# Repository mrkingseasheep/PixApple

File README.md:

# PixApple

PixApple is designed as a RP2040 breakout board. It features 8 general use GPIOs, 1 SPI interface, 1 I2C interface, 4 ADC channels, 4 PWM channels and a CAN bus.
I designed it because I wanted a board that I could use for general purpose robotics projects. Being from FRC, a CAN bus was a must so I added the CAN bus onto the RP2040 with split terminations.
The Roborio is like 2000CAD so it's so far out of reach its funny. Of course, I don't need the real time OS or the robust nature of the thing, I just want to drive a lil car or something. So I created this!
Building this project really gave me a greater understanding of what went on undernearth the Roborio (I never did open it) and everything actually kinda makes sense now.
I chose the RP2040 because it is cheap, decently powerful for the basic robotics I plan on doing with it and is also what I'm used to.
Additionally, I chose the 0603 SMT format because I wanted to be able to fix any problems I have later on with this board.
This being V1.0, many of the values are not tested and I wanted the ability to fix them if anything happened.
Finally, there are test points scattered around the board for easy debugging.

## What I've gained

Total time spent: 51 hours (I'm still so slow at KiCAD) (the redo didn't help)

This is my first semi-intermediate project and I wanted to learn more about ICs in general. I've incorporated: wide power traces, equal length wires and a ground pour on top and bottom in this project.

## BOM

| Quantity | Value                       | Cost    | URL                                                                                                                                                    |
| -------- | --------------------------- | ------- | ------------------------------------------------------------------------------------------------------------------------------------------------------ |
| 17       | Capacitor 100n              | 0.068   | https://www.aliexpress.com/item/1005002782324319.html                                                                                                  |
| 3        | Capacitor 1u                | 0.012   | https://www.aliexpress.com/item/1005002782324319.html                                                                                                  |
| 2        | Capacitor 10n               | 0.008   | https://www.aliexpress.com/item/1005002782324319.html                                                                                                  |
| 2        | Capacitor 10u               | 0.008   | https://www.aliexpress.com/item/1005002782324319.html                                                                                                  |
| 1        | Capacitor 4.7n              | 0.004   | https://www.aliexpress.com/item/1005002782324319.html                                                                                                  |
| 2        | TVS Diode RCLAMP0502BA      | 2.50    | https://www.digikey.ca/en/products/detail/semtech-corporation/RCLAMP0502BATCT/2603604?s=N4IgTCBcDaICoDUDKACAIgSwPYBMCmKASgMIAyAggLIAKADAKy1gBC5IAugL5A |
| 1        | SMF5V0A                     | 0.25    | https://www.digikey.ca/en/products/detail/vishay-general-semiconductor-diodes-division/SMF5V0A-E3-08/1680585                                           |
| 1        | 1N4148W                     | 0.014   | https://www.aliexpress.com/item/4000685043735.html                                                                                                     |
| 3        | LED                         | 0.0525  | https://www.aliexpress.com/item/1005006211269173.html                                                                                                  |
| 1        | USB_C_Receptacle_USB2.0_16P | 0.1875  | https://www.aliexpress.com/item/1005008515699009.html                                                                                                  |
| 22       | 2.54mm Pins Male            | 0.20295 | https://www.aliexpress.com/item/4001198421663.html                                                                                                     |
| 2        | Resistor 27R                | 0.01    | https://www.aliexpress.com/item/1005007902452631.html                                                                                                  |
| 3        | Resistor 1K                 | 0.015   | https://www.aliexpress.com/item/1005007902452631.html                                                                                                  |
| 5        | Resistor DNF                | 0.025   | https://www.aliexpress.com/item/1005007902452631.html                                                                                                  |
| 2        | Resistor 60R                | 0.01    | https://www.aliexpress.com/item/1005007902452631.html                                                                                                  |
| 5        | Resistor 10K                | 0.025   | https://www.aliexpress.com/item/1005007902452631.html                                                                                                  |
| 3        | Resistor 220R               | 0.015   | https://www.aliexpress.com/item/1005007902452631.html                                                                                                  |
| 2        | Resistor 5.1K               | 0.01    | https://www.aliexpress.com/item/1005007902452631.html                                                                                                  |
| 1        | RP2040                      | 1.29    | https://www.canakit.com/raspberry-pi-rp2040.html?cid=cad&src=raspberrypi                                                                               |
| 1        | W25Q128JVS                  |         | JLCPCB Assembly                                                                                                                                        |
| 1        | NCP1117-3.3_SOT223          |         | JLCPCB Assembly                                                                                                                                        |
| 1        | MCP2515-xSO                 |         | JLCPCB Assembly                                                                                                                                        |
| 1        | TCAN337G                    |         | JLCPCB Assembly                                                                                                                                        |
| 1        | ASE-12MHz                   | 1.56    | https://www.mouser.ca/ProductDetail/ABRACON/ASE-12.000MHZ-ET?qs=uDmhV2jwPRcj2BLg3gv24Q%3D%3D                                                           |
| 1        | ASE-16MHz                   | 1.53    | https://www.mouser.ca/ProductDetail/ABRACON/ASE-16.000MHZ-LC-T?qs=gt1LBUVyoHnfDWzQTg2whA%3D%3D                                                         |
| 1        | PCB                         | 75      | JLCPCB Assembly                                                                                                                                        |
| 2        | Heat set insert             | 0.10    | https://www.aliexpress.com/item/1005007653131713.html                                                                                                  |
| 2        | M2                          | 0.08    | https://www.aliexpress.com/item/32810872544.html                                                                                                       |
| 1        | Case                        | 5       | Printing Legion                                                                                                                                        |

Total: 80 CAD

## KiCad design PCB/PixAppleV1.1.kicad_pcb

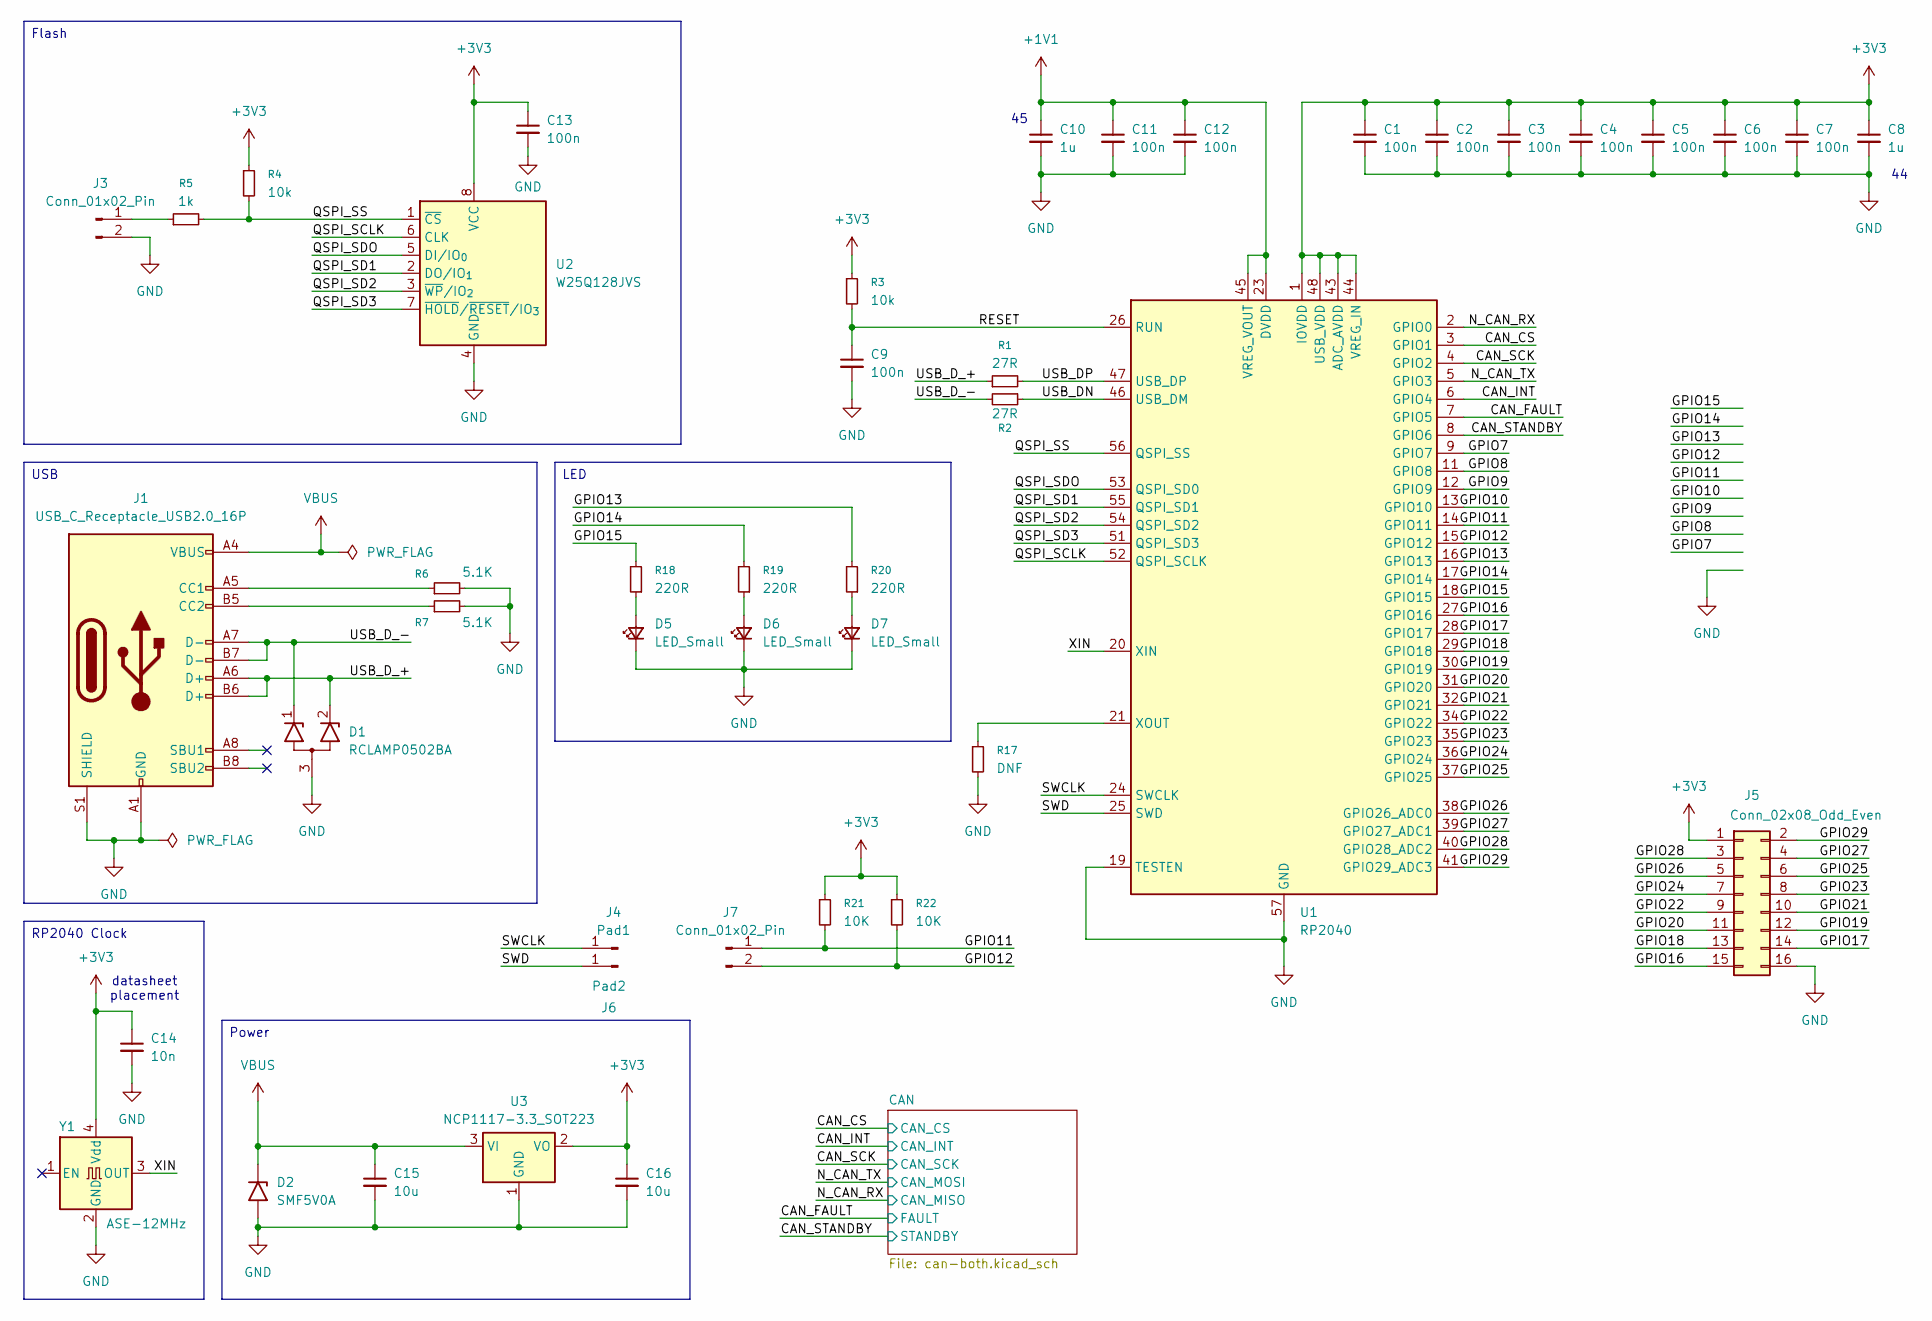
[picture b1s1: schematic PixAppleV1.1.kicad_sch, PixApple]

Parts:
C1, C2, C3, C4, C5, C6, C7, C9, C11, C12, C13: 100n; C_0603_1608Metric_Pad1.08x0.95mm_HandSolder
C8, C10: 1u; C_0603_1608Metric_Pad1.08x0.95mm_HandSolder
C14: 10n; C_0603_1608Metric_Pad1.08x0.95mm_HandSolder
C15, C16: 10u; C_0603_1608Metric_Pad1.08x0.95mm_HandSolder
D1: RCLAMP0502BA; SOT-416
D2: SMF5V0A; D_SMF
D5, D6, D7: LED_Small; LED_0603_1608Metric_Pad1.05x0.95mm_HandSolder
J1: USB_C_Receptacle_USB2.0_16P; USB_C_Receptacle_GCT_USB4105-xx-A_16P_TopMnt_Horizontal
J3, J7: Conn_01x02_Pin; PinHeader_1x02_P2.54mm_Vertical
J4: Pad1; TestPoint_Pad_1.0x1.0mm
J5: Conn_02x08_Odd_Even; PinHeader_2x08_P2.54mm_Vertical
J6: Pad2; TestPoint_Pad_1.0x1.0mm
R1, R2: 27R; R_0603_1608Metric_Pad0.98x0.95mm_HandSolder
R3, R4: 10k; R_0603_1608Metric_Pad0.98x0.95mm_HandSolder
R5: 1k; R_0603_1608Metric_Pad0.98x0.95mm_HandSolder
R6, R7: 5.1K; R_0603_1608Metric_Pad0.98x0.95mm_HandSolder
R17: DNF; R_0603_1608Metric_Pad0.98x0.95mm_HandSolder
R18, R19, R20: 220R; R_0603_1608Metric_Pad0.98x0.95mm_HandSolder
R21, R22: 10K; R_0603_1608Metric_Pad0.98x0.95mm_HandSolder
U1: RP2040; QFN-56-1EP_7x7mm_P0.4mm_EP3.2x3.2mm
U2: W25Q128JVS; SOIC-8_5.3x5.3mm_P1.27mm
U3: NCP1117-3.3_SOT223; SOT-223-3_TabPin2
Y1: ASE-12MHz; Oscillator_SMD_Abracon_ASE-4Pin_3.2x2.5mm

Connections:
+1V1: C10.1, C11.1, C12.1, U1.23 (DVDD), U1.45 (VREG_VOUT), U1.50 (DVDD)
+3V3: C1.1, C2.1, C3.1, C4.1, C5.1, C6.1, C7.1, C8.1, C13.1, C14.1, C16.1, J5.1, R3.1, R4.1, R21.1, R22.1, U1.1 (IOVDD), U1.10 (IOVDD), U1.22 (IOVDD), U1.33 (IOVDD), U1.42 (IOVDD), U1.43 (ADC_AVDD), U1.44 (VREG_IN), U1.48 (USB_VDD), U1.49 (IOVDD), U2.8 (VCC), U3.2 (VO), Y1.4 (Vdd); also elsewhere on the board
/CAN_CS: U1.3 (GPIO1); also elsewhere on the board
/CAN_FAULT: U1.7 (GPIO5); also elsewhere on the board
/CAN_INT: U1.6 (GPIO4); also elsewhere on the board
/CAN_SCK: U1.4 (GPIO2); also elsewhere on the board
/CAN_STANDBY: U1.8 (GPIO6); also elsewhere on the board
/GPIO7: U1.9 (GPIO7); also elsewhere on the board
/GPIO8: U1.11 (GPIO8)
/GPIO9: U1.12 (GPIO9); also elsewhere on the board
/GPIO10: U1.13 (GPIO10); also elsewhere on the board
/GPIO11: J7.1, R21.2, U1.14 (GPIO11)
/GPIO12: J7.2, R22.2, U1.15 (GPIO12)
/GPIO13: R20.2, U1.16 (GPIO13)
/GPIO14: R19.2, U1.17 (GPIO14)
/GPIO15: R18.2, U1.18 (GPIO15)
/GPIO16: J5.15, U1.27 (GPIO16)
/GPIO17: J5.14, U1.28 (GPIO17)
/GPIO18: J5.13, U1.29 (GPIO18)
/GPIO19: J5.12, U1.30 (GPIO19)
/GPIO20: J5.11, U1.31 (GPIO20)
/GPIO21: J5.10, U1.32 (GPIO21)
/GPIO22: J5.9, U1.34 (GPIO22)
/GPIO23: J5.8, U1.35 (GPIO23)
/GPIO24: J5.7, U1.36 (GPIO24)
/GPIO25: J5.6, U1.37 (GPIO25)
/GPIO26: J5.5, U1.38 (GPIO26_ADC0)
/GPIO27: J5.4, U1.39 (GPIO27_ADC1)
/GPIO28: J5.3, U1.40 (GPIO28_ADC2)
/GPIO29: J5.2, U1.41 (GPIO29_ADC3)
/N_CAN_RX: U1.2 (GPIO0); also elsewhere on the board
/N_CAN_TX: U1.5 (GPIO3); also elsewhere on the board
/QSPI_SCLK: U1.52 (QSPI_SCLK), U2.6 (CLK)
/QSPI_SD1: U1.55 (QSPI_SD1), U2.2 (DO/IO_{1})
/QSPI_SD2: U1.54 (QSPI_SD2), U2.3 (~WP/IO_{2})
/QSPI_SD3: U1.51 (QSPI_SD3), U2.7 (~HOLD/~RESET/IO_{3})
/QSPI_SDO: U1.53 (QSPI_SD0), U2.5 (DI/IO_{0})
/QSPI_SS: R4.2, R5.2, U1.56 (QSPI_SS), U2.1 (~CS)
/RESET: C9.1, R3.2, U1.26 (RUN)
/SWCLK: J4.1, U1.24 (SWCLK); also elsewhere on the board
/SWD: J6.1, U1.25 (SWD); also elsewhere on the board
/USB_DN: R2.1, U1.46 (USB_DM)
/USB_DP: R1.2, U1.47 (USB_DP)
/USB_D_+: D1.2 (K2), J1.A6 (D+), J1.B6 (D+), R1.1; also elsewhere on the board
/USB_D_-: D1.1 (K1), J1.A7 (D-), J1.B7 (D-), R2.2; also elsewhere on the board
/XIN: U1.20 (XIN), Y1.3 (OUT)
GND: C1.2, C2.2, C3.2, C4.2, C5.2, C6.2, C7.2, C8.2, C9.2, C10.2, C11.2, C12.2, C13.2, C14.2, C15.2, C16.2, D1.3 (A), D2.2 (A2), D5.1 (K), D6.1 (K), D7.1 (K), J1.A1 (GND), J1.A12 (GND), J1.B1 (GND), J1.B12 (GND), J1.S1 (SHIELD), J3.2, J5.16, R6.2, R7.2, R17.2, U1.19 (TESTEN), U1.57 (GND), U2.4 (GND), U3.1 (GND), Y1.2 (GND); also elsewhere on the board
unnamed: D5.2 (A), R18.1
unnamed: D6.2 (A), R19.1
unnamed: D7.2 (A), R20.1
unnamed: J1.A5 (CC1), R6.1
unnamed: J1.B5 (CC2), R7.1
unnamed: J3.1, R5.1
unnamed: R17.1, U1.21 (XOUT)
VBUS: C15.1, D2.1 (A1), J1.A4 (VBUS), J1.A9 (VBUS), J1.B4 (VBUS), J1.B9 (VBUS), U3.3 (VI); also elsewhere on the board

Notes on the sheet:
datasheet placement
RP2040 Clock
Power
LED
USB
Flash

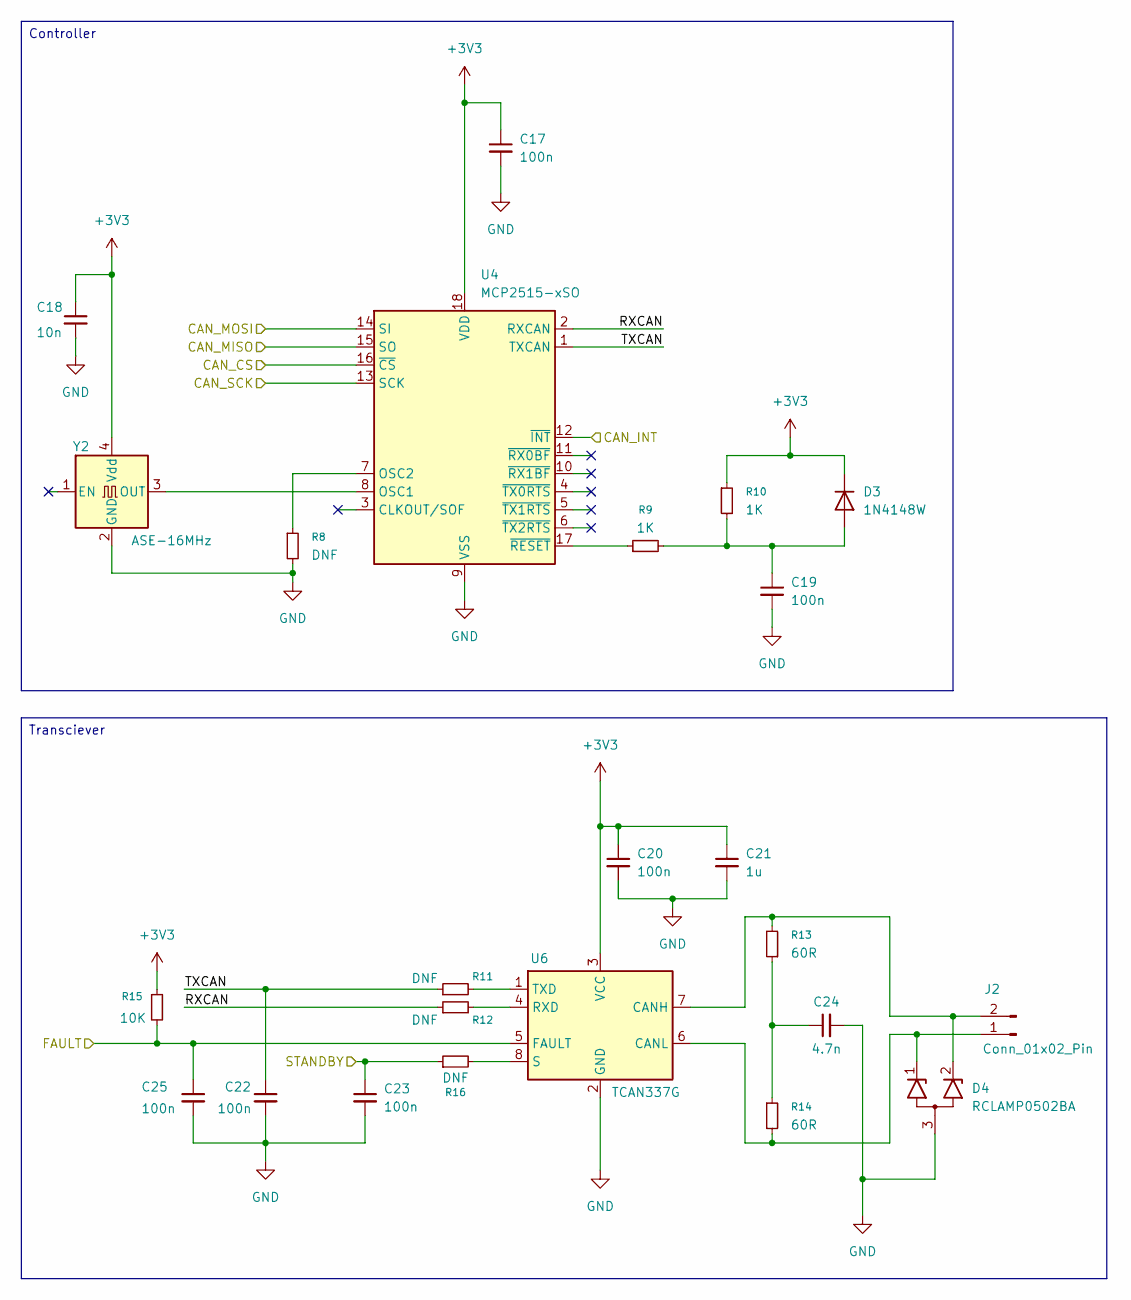
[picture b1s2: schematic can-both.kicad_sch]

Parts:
C17, C19, C20, C22, C23, C25: 100n; C_0603_1608Metric_Pad1.08x0.95mm_HandSolder
C18: 10n; C_0603_1608Metric_Pad1.08x0.95mm_HandSolder
C21: 1u; C_0603_1608Metric_Pad1.08x0.95mm_HandSolder
C24: 4.7n; C_0603_1608Metric_Pad1.08x0.95mm_HandSolder
D3: 1N4148W; D_SOD-123
D4: RCLAMP0502BA; SOT-416
J2: Conn_01x02_Pin; PinHeader_1x02_P2.54mm_Vertical
R8, R11, R12, R16: DNF; R_0603_1608Metric_Pad0.98x0.95mm_HandSolder
R9, R10: 1K; R_0603_1608Metric_Pad0.98x0.95mm_HandSolder
R13, R14: 60R; R_0603_1608Metric_Pad0.98x0.95mm_HandSolder
R15: 10K; R_0603_1608Metric_Pad0.98x0.95mm_HandSolder
U4: MCP2515-xSO; SOIC-18W_7.5x11.6mm_P1.27mm
U6: TCAN337G; SOIC-8_3.9x4.9mm_P1.27mm
Y2: ASE-16MHz; Oscillator_SMD_Abracon_ASE-4Pin_3.2x2.5mm

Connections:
+3V3: C17.1, C18.1, C20.1, C21.1, D3.1 (K), R10.1, R15.1, U4.18 (VDD), U6.3 (VCC), Y2.4 (Vdd); also elsewhere on the board
/CAN/RXCAN: R12.1, U4.2 (RXCAN)
/CAN/TXCAN: C22.1, R11.1, U4.1 (TXCAN)
/CAN_CS: U4.16 (~CS); also elsewhere on the board
/CAN_FAULT: C25.1, R15.2, U6.5 (FAULT); also elsewhere on the board
/CAN_INT: U4.12 (~INT); also elsewhere on the board
/CAN_SCK: U4.13 (SCK); also elsewhere on the board
/CAN_STANDBY: C23.1, R16.1; also elsewhere on the board
/N_CAN_RX: U4.15 (SO); also elsewhere on the board
/N_CAN_TX: U4.14 (SI); also elsewhere on the board
GND: C17.2, C18.2, C19.2, C20.2, C21.2, C22.2, C23.2, C24.2, C25.2, D4.3 (A), R8.2, U4.9 (VSS), U6.2 (GND), Y2.2 (GND); also elsewhere on the board
unnamed: C24.1, R13.1, R14.1
unnamed: C19.1, D3.2 (A), R9.2, R10.2
unnamed: D4.1 (K1), J2.1, R14.2, U6.6 (CANL)
unnamed: D4.2 (K2), J2.2, R13.2, U6.7 (CANH)
unnamed: U4.8 (OSC1), Y2.3 (OUT)
unnamed: R8.1, U4.7 (OSC2)
unnamed: R9.1, U4.17 (~RESET)
unnamed: R12.2, U6.4 (RXD)
unnamed: R16.2, U6.8 (S)
unnamed: R11.2, U6.1 (TXD)

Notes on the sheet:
Transciever
Controller

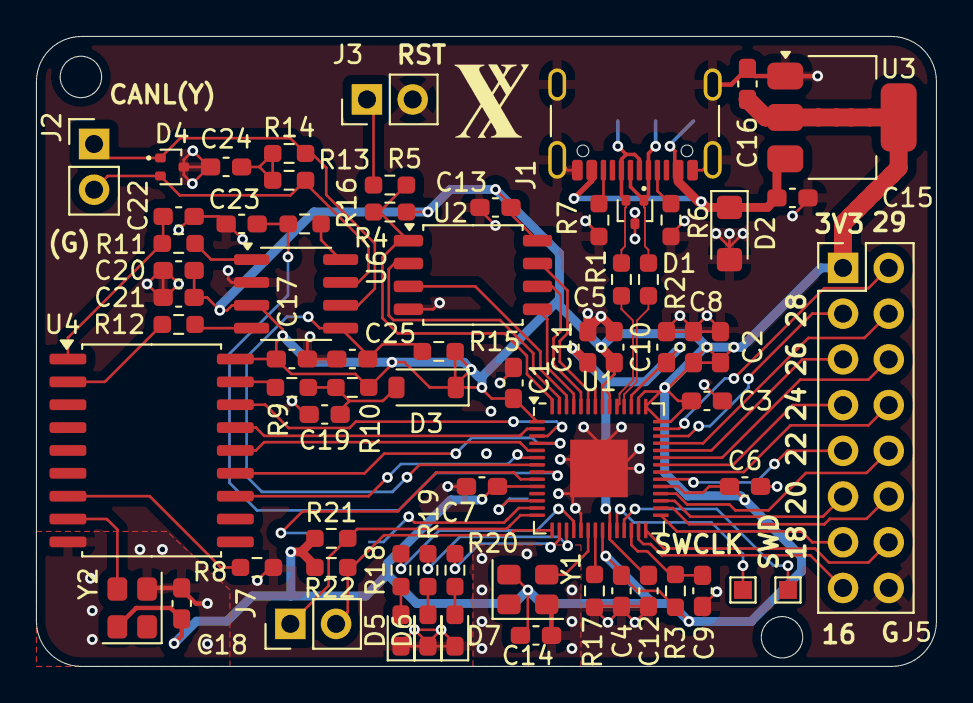
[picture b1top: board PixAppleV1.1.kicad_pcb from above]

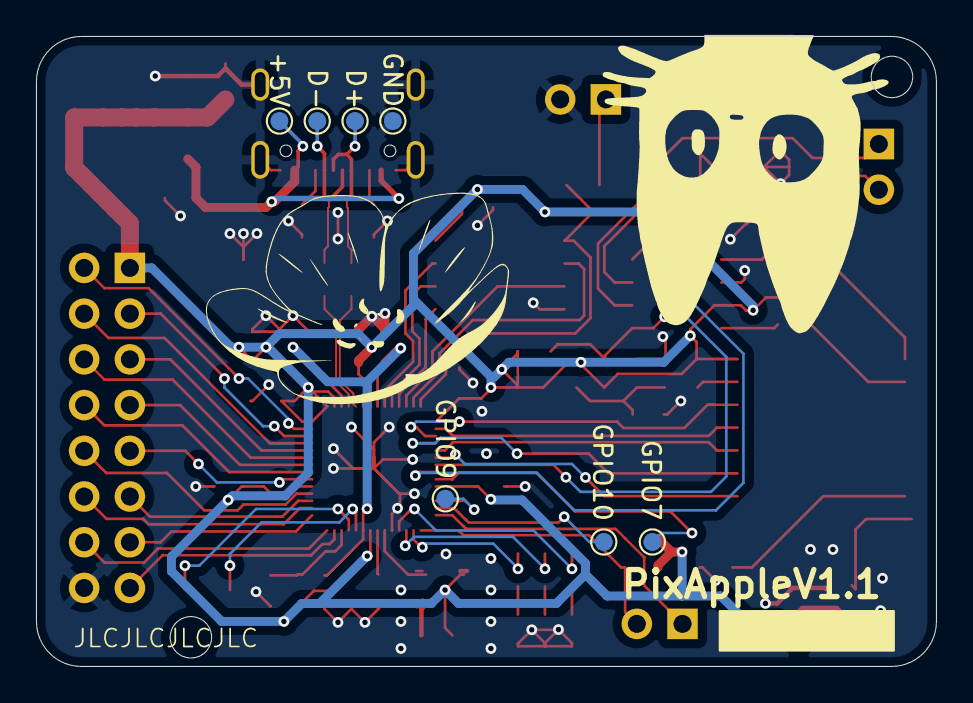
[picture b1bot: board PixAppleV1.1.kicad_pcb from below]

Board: 4 copper layers, 50.0 x 35.0 mm, 75 parts (7 on the bottom side), 66 nets.

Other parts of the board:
+5V: TestPoint_Pad_D1.0mm
D+: TestPoint_Pad_D1.0mm
D-: TestPoint_Pad_D1.0mm
GND: TestPoint_Pad_D1.0mm
GPIO7, GPIO9, GPIO10: TestPoint_Pad_D1.0mm
SWCLK: Pad1; TestPoint_Pad_1.0x1.0mm
SWD: Pad2; TestPoint_Pad_1.0x1.0mm

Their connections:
/GPIO7: GPIO7.1; also elsewhere on the board
/GPIO9: GPIO9.1; also elsewhere on the board
/GPIO10: GPIO10.1; also elsewhere on the board
/SWCLK: SWCLK.1; also elsewhere on the board
/SWD: SWD.1; also elsewhere on the board
/USB_D_+: D+.1; also elsewhere on the board
/USB_D_-: D-.1; also elsewhere on the board
GND: GND.1; also elsewhere on the board
VBUS: +5V.1; also elsewhere on the board

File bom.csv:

"Quantity","Value","Cost","URL"
"17","Capacitor 100n","0.068","https://www.aliexpress.com/item/1005002782324319.html"
"3","Capacitor 1u","0.012","https://www.aliexpress.com/item/1005002782324319.html"
"2","Capacitor 10n","0.008","https://www.aliexpress.com/item/1005002782324319.html"
"2","Capacitor 10u","0.008","https://www.aliexpress.com/item/1005002782324319.html"
"1","Capacitor 4.7n","0.004","https://www.aliexpress.com/item/1005002782324319.html"
"2","TVS Diode RCLAMP0502BA","2.50","https://www.digikey.ca/en/products/detail/semtech-corporatio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"
"1","SMF5V0A","0.25","https://www.digikey.ca/en/products/detail/vishay-general-sem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"
"1","1N4148W","0.014","https://www.aliexpress.com/item/4000685043735.html"
"3","LED","0.0525","https://www.aliexpress.com/item/1005006211269173.html"
"1","USB_C_Receptacle_USB2.0_16P","0.1875","https://www.aliexpress.com/item/1005008515699009.html"
"22","2.54mm Pins Male","0.20295","https://www.aliexpress.com/item/4001198421663.html"
"2","Resistor 27R","0.01","https://www.aliexpress.com/item/1005007902452631.html"
"3","Resistor 1K","0.015","https://www.aliexpress.com/item/1005007902452631.html"
"5","Resistor DNF","0.025","https://www.aliexpress.com/item/1005007902452631.html"
"2","Resistor 60R","0.01","https://www.aliexpress.com/item/1005007902452631.html"
"5","Resistor 10K","0.025","https://www.aliexpress.com/item/1005007902452631.html"
"3","Resistor 220R","0.015","https://www.aliexpress.com/item/1005007902452631.html"
"2","Resistor 5.1K","0.01","https://www.aliexpress.com/item/1005007902452631.html"
"1","RP2040","1.29","https://www.canakit.com/raspberry-pi-rp2040.html?cid=cad&src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"
"1","W25Q128JVS","","JLCPCB Assembly"
"1","NCP1117-3.3_SOT223","","JLCPCB Assembly"
"1","MCP2515-xSO","","JLCPCB Assembly"
"1","TCAN337G","","JLCPCB Assembly"
"1","ASE-12MHz","1.56","https://www.mouser.ca/ProductDetail/ABRACON/ASE-12.000MHZ-ET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"
"1","ASE-16MHz","1.53","https://www.mouser.ca/ProductDetail/ABRACON/ASE-16.000MHZ-LC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"
"1","PCB","75","JLCPCB Assembly"

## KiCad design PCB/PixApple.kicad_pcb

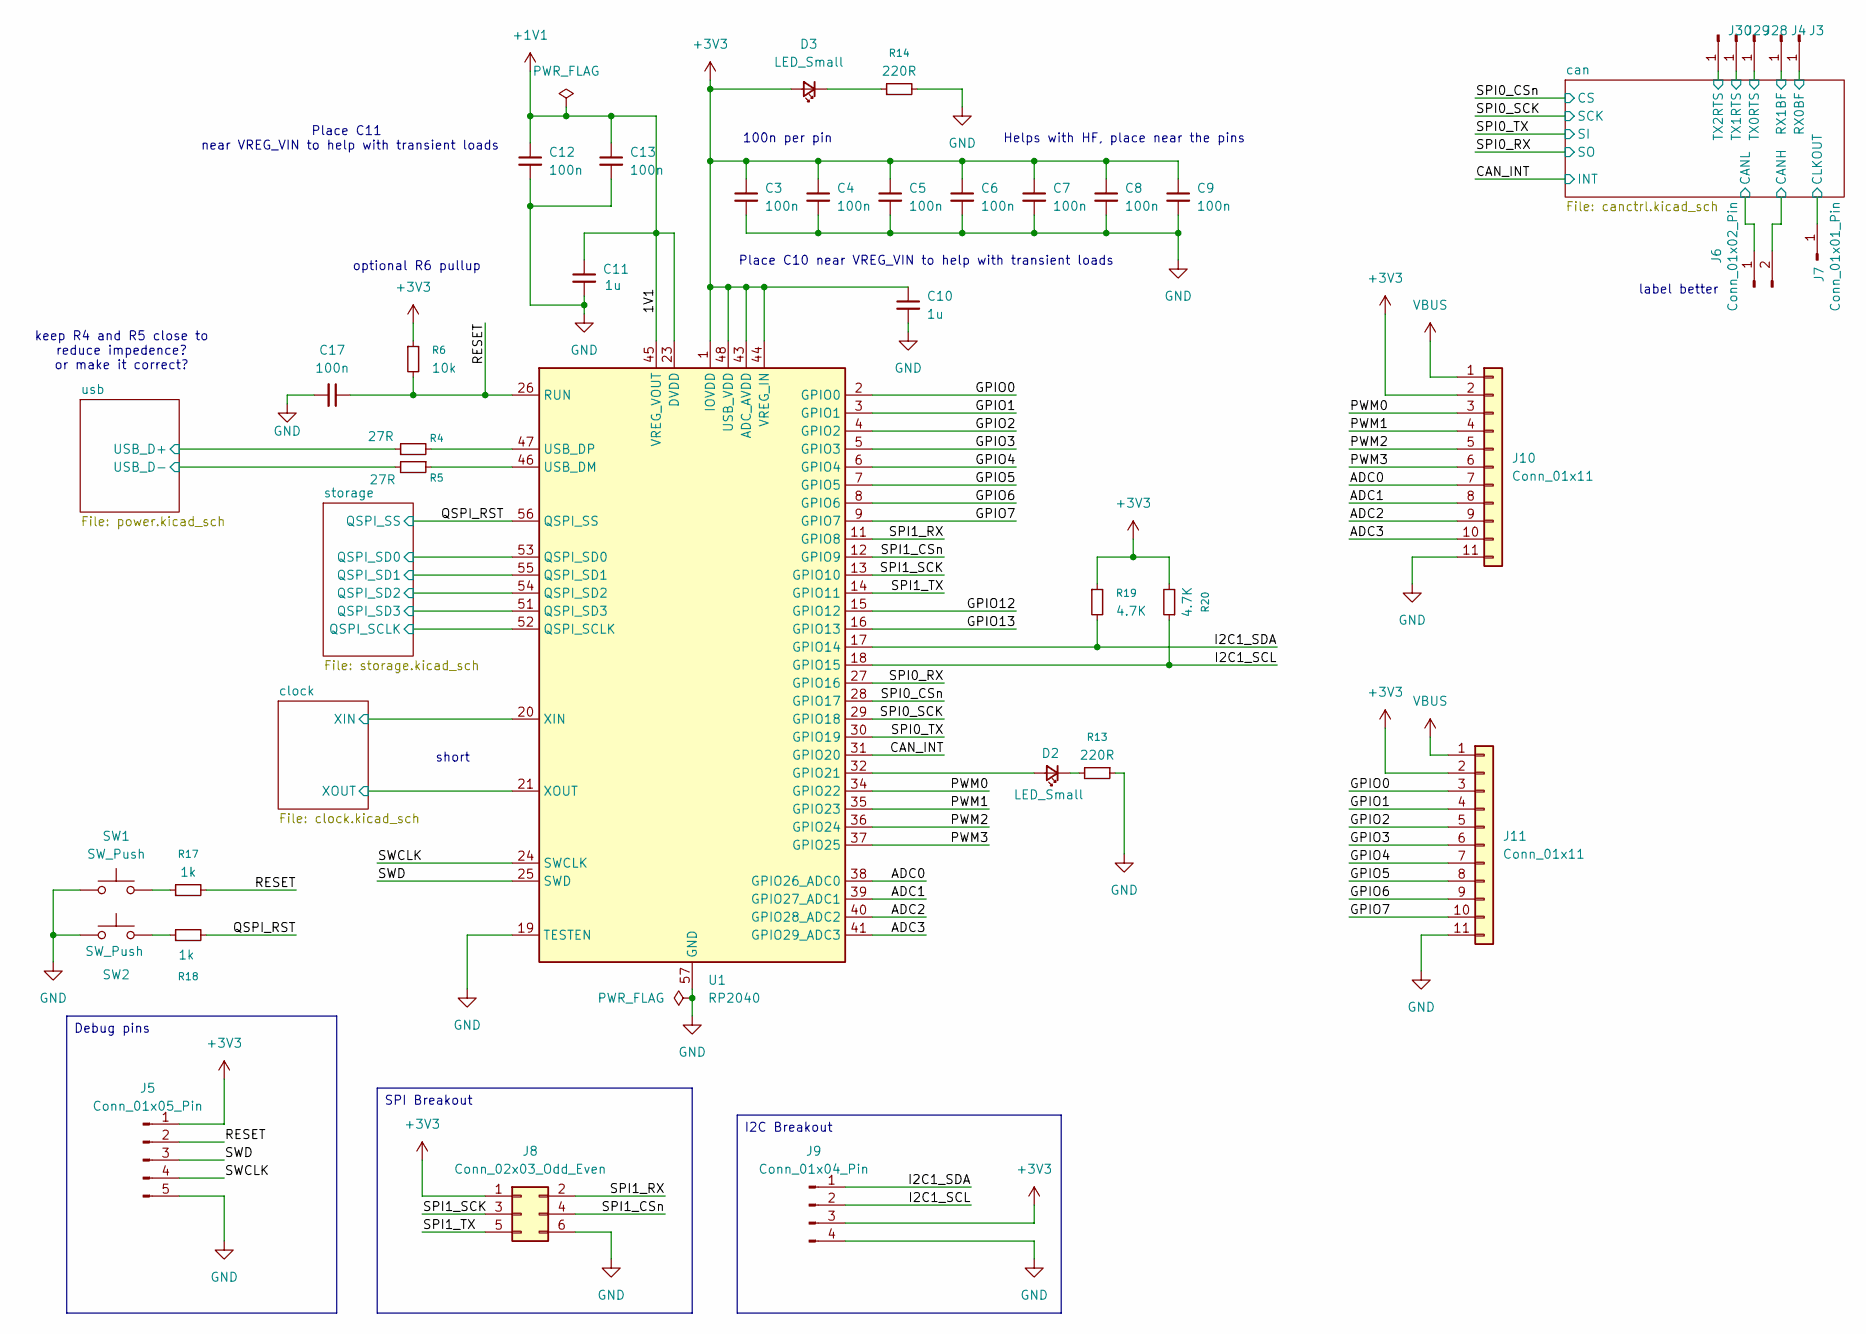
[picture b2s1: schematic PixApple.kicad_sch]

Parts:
C3, C4, C5, C6, C7, C8, C9, C12, C13, C17: 100n; C_0603_1608Metric_Pad1.08x0.95mm_HandSolder
C10, C11: 1u; C_0603_1608Metric_Pad1.08x0.95mm_HandSolder
D2, D3: LED_Small; LED_0603_1608Metric_Pad1.05x0.95mm_HandSolder
J3, J4, J7, J28, J29, J30: Conn_01x01_Pin; TestPoint_Pad_1.0x1.0mm
J5: Conn_01x05_Pin; PinHeader_1x05_P2.54mm_Vertical
J6: Conn_01x02_Pin; PinHeader_1x02_P2.54mm_Vertical
J8: Conn_02x03_Odd_Even; PinHeader_2x03_P2.54mm_Vertical
J9: Conn_01x04_Pin; PinHeader_1x04_P2.54mm_Vertical
J10, J11: Conn_01x11; PinHeader_1x11_P2.54mm_Vertical
R4, R5: 27R; R_0603_1608Metric_Pad0.98x0.95mm_HandSolder
R6: 10k; R_0603_1608Metric_Pad0.98x0.95mm_HandSolder
R13, R14: 220R; R_0603_1608Metric_Pad0.98x0.95mm_HandSolder
R17, R18: 1k; R_0603_1608Metric_Pad0.98x0.95mm_HandSolder
R19, R20: 4.7K; R_0603_1608Metric_Pad0.98x0.95mm_HandSolder
SW1, SW2: SW_Push; SW_PUSH_6mm
U1: RP2040; QFN-56-1EP_7x7mm_P0.4mm_EP3.2x3.2mm

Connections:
+1V1: C11.1, C12.1, C13.1, U1.23 (DVDD), U1.45 (VREG_VOUT), U1.50 (DVDD)
+3V3: C3.1, C4.1, C5.1, C6.1, C7.1, C8.1, C9.1, C10.1, D3.2 (A), J5.1, J8.1, J9.3, J10.2, J11.2, R6.1, R19.1, R20.2, U1.1 (IOVDD), U1.10 (IOVDD), U1.22 (IOVDD), U1.33 (IOVDD), U1.42 (IOVDD), U1.43 (ADC_AVDD), U1.44 (VREG_IN), U1.48 (USB_VDD), U1.49 (IOVDD); also elsewhere on the board
/ADC0: J10.7, U1.38 (GPIO26_ADC0)
/ADC1: J10.8, U1.39 (GPIO27_ADC1)
/ADC2: J10.9, U1.40 (GPIO28_ADC2)
/ADC3: J10.10, U1.41 (GPIO29_ADC3)
/CAN_INT: U1.31 (GPIO20); also elsewhere on the board
/GPIO0: J11.3, U1.2 (GPIO0)
/GPIO1: J11.4, U1.3 (GPIO1)
/GPIO2: J11.5, U1.4 (GPIO2)
/GPIO3: J11.6, U1.5 (GPIO3)
/GPIO4: J11.7, U1.6 (GPIO4)
/GPIO5: J11.8, U1.7 (GPIO5)
/GPIO6: J11.9, U1.8 (GPIO6)
/GPIO7: J11.10, U1.9 (GPIO7)
/GPIO12: U1.15 (GPIO12)
/GPIO13: U1.16 (GPIO13)
/I2C1_SCL: J9.2, R20.1, U1.18 (GPIO15)
/I2C1_SDA: J9.1, R19.2, U1.17 (GPIO14)
/PWM0: J10.3, U1.34 (GPIO22)
/PWM1: J10.4, U1.35 (GPIO23)
/PWM2: J10.5, U1.36 (GPIO24)
/PWM3: J10.6, U1.37 (GPIO25)
/QSPI_RST: R18.2, U1.56 (QSPI_SS); also elsewhere on the board
/RESET: C17.1, J5.2, R6.2, R17.2, U1.26 (RUN)
/SPI0_CSn: U1.28 (GPIO17); also elsewhere on the board
/SPI0_RX: U1.27 (GPIO16); also elsewhere on the board
/SPI0_SCK: U1.29 (GPIO18); also elsewhere on the board
/SPI0_TX: U1.30 (GPIO19); also elsewhere on the board
/SPI1_CSn: J8.4, U1.12 (GPIO9)
/SPI1_RX: J8.2, U1.11 (GPIO8)
/SPI1_SCK: J8.3, U1.13 (GPIO10)
/SPI1_TX: J8.5, U1.14 (GPIO11)
/SWCLK: J5.4, U1.24 (SWCLK)
/SWD: J5.3, U1.25 (SWD)
/can/CANH: J6.2; also elsewhere on the board
/can/CANL: J6.1; also elsewhere on the board
/can/CLKOUT: J7.1; also elsewhere on the board
/can/RX0BF: J3.1; also elsewhere on the board
/can/RX1BF: J4.1; also elsewhere on the board
/can/TX0RTS: J28.1; also elsewhere on the board
/can/TX1RTS: J29.1; also elsewhere on the board
/can/TX2RTS: J30.1; also elsewhere on the board
/clock/XIN: U1.20 (XIN); also elsewhere on the board
/clock/XOUT: U1.21 (XOUT); also elsewhere on the board
/storage/QSPI_SCLK: U1.52 (QSPI_SCLK); also elsewhere on the board
/storage/QSPI_SD0: U1.53 (QSPI_SD0); also elsewhere on the board
/storage/QSPI_SD1: U1.55 (QSPI_SD1); also elsewhere on the board
/storage/QSPI_SD2: U1.54 (QSPI_SD2); also elsewhere on the board
/storage/QSPI_SD3: U1.51 (QSPI_SD3); also elsewhere on the board
/usb/USB_D+: R4.1; also elsewhere on the board
/usb/USB_D-: R5.2; also elsewhere on the board
GND: C3.2, C4.2, C5.2, C6.2, C7.2, C8.2, C9.2, C10.2, C11.2, C12.2, C13.2, C17.2, J5.5, J8.6, J9.4, J10.11, J11.11, R13.1, R14.2, SW1.1, SW2.1, U1.19 (TESTEN), U1.57 (GND); also elsewhere on the board
unnamed: D2.2 (A), U1.32 (GPIO21)
unnamed: D2.1 (K), R13.2
unnamed: D3.1 (K), R14.1
unnamed: R17.1, SW1.2
unnamed: R18.1, SW2.2
unnamed: R5.1, U1.46 (USB_DM)
unnamed: R4.2, U1.47 (USB_DP)
VBUS: J10.1, J11.1; also elsewhere on the board

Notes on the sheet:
optional R6 pullup
keep R4 and R5 close to reduce impedence? or make it correct?
100n per pin
label better
Place C10 near VREG_VIN to help with transient loads
Helps with HF, place near the pins
short
Place C11 near VREG_VIN to help with transient loads
Debug pins
I2C Breakout
SPI Breakout

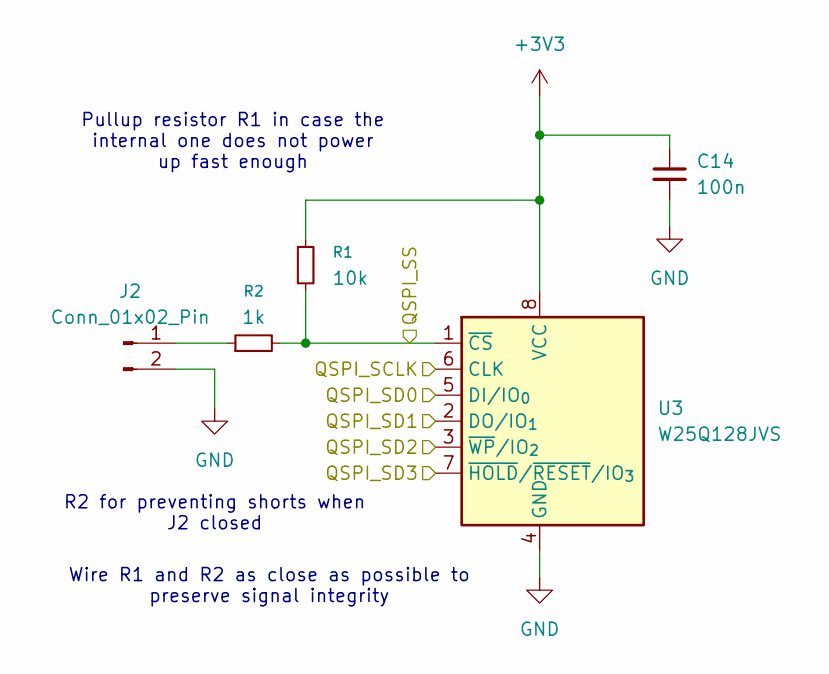
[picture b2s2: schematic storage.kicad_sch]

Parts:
C14: 100n; C_0603_1608Metric_Pad1.08x0.95mm_HandSolder
J2: Conn_01x02_Pin; PinHeader_1x02_P2.54mm_Vertical
R1: 10k; R_0603_1608Metric_Pad0.98x0.95mm_HandSolder
R2: 1k; R_0603_1608Metric_Pad0.98x0.95mm_HandSolder
U3: W25Q128JVS; SOIC-8_5.3x5.3mm_P1.27mm

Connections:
+3V3: C14.1, R1.1, U3.8 (VCC); also elsewhere on the board
/QSPI_RST: R1.2, R2.2, U3.1 (~CS); also elsewhere on the board
/storage/QSPI_SCLK: U3.6 (CLK); also elsewhere on the board
/storage/QSPI_SD0: U3.5 (DI/IO_{0}); also elsewhere on the board
/storage/QSPI_SD1: U3.2 (DO/IO_{1}); also elsewhere on the board
/storage/QSPI_SD2: U3.3 (~WP/IO_{2}); also elsewhere on the board
/storage/QSPI_SD3: U3.7 (~HOLD/~RESET/IO_{3}); also elsewhere on the board
GND: C14.2, J2.2, U3.4 (GND); also elsewhere on the board
unnamed: J2.1, R2.1

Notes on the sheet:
Wire R1 and R2 as close as possible to preserve signal integrity
Pullup resistor R1 in case the internal one does not power up fast enough
R2 for preventing shorts when J2 closed

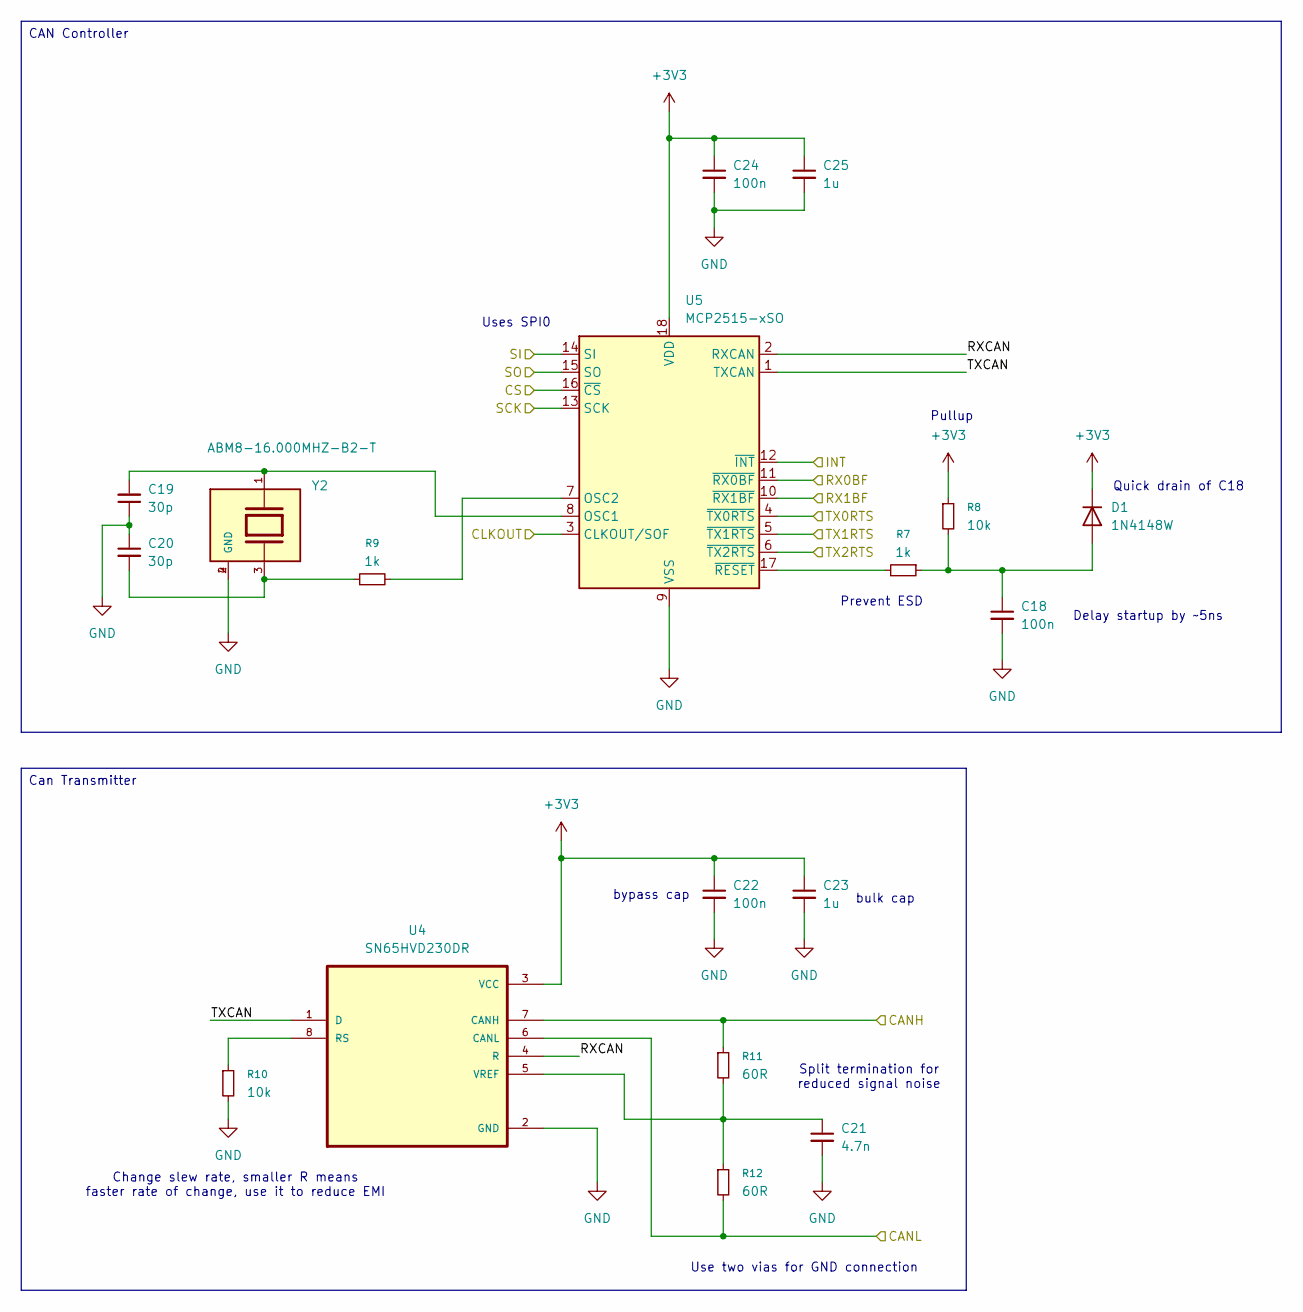
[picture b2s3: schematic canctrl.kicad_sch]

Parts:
C18, C22, C24: 100n; C_0603_1608Metric_Pad1.08x0.95mm_HandSolder
C19, C20: 30p; C_0603_1608Metric_Pad1.08x0.95mm_HandSolder
C21: 4.7n; C_0603_1608Metric_Pad1.08x0.95mm_HandSolder
C23, C25: 1u; C_0603_1608Metric_Pad1.08x0.95mm_HandSolder
D1: 1N4148W; D_SOD-123
R7, R9: 1k; R_0603_1608Metric_Pad0.98x0.95mm_HandSolder
R8, R10: 10k; R_0603_1608Metric_Pad0.98x0.95mm_HandSolder
R11, R12: 60R; R_0603_1608Metric_Pad0.98x0.95mm_HandSolder
U4: SN65HVD230DR; SOIC127P599X175-8N
U5: MCP2515-xSO; SOIC-18W_7.5x11.6mm_P1.27mm
Y2: ABM8-16.000MHZ-B2-T; XTAL_ABM8-16.000MHZ-B2-T; PARTREV 44041

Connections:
+3V3: C22.1, C23.1, C24.1, C25.1, D1.1 (K), R8.1, U4.3 (VCC), U5.18 (VDD); also elsewhere on the board
/CAN_INT: U5.12 (~INT); also elsewhere on the board
/SPI0_CSn: U5.16 (~CS); also elsewhere on the board
/SPI0_RX: U5.15 (SO); also elsewhere on the board
/SPI0_SCK: U5.13 (SCK); also elsewhere on the board
/SPI0_TX: U5.14 (SI); also elsewhere on the board
/can/CANH: R11.1, U4.7 (CANH); also elsewhere on the board
/can/CANL: R12.2, U4.6 (CANL); also elsewhere on the board
/can/CLKOUT: U5.3 (CLKOUT/SOF); also elsewhere on the board
/can/RX0BF: U5.11 (~RX0BF); also elsewhere on the board
/can/RX1BF: U5.10 (~RX1BF); also elsewhere on the board
/can/RXCAN: U4.4 (R), U5.2 (RXCAN)
/can/TX0RTS: U5.4 (~TX0RTS); also elsewhere on the board
/can/TX1RTS: U5.5 (~TX1RTS); also elsewhere on the board
/can/TX2RTS: U5.6 (~TX2RTS); also elsewhere on the board
/can/TXCAN: U4.1 (D), U5.1 (TXCAN)
GND: C18.2, C19.1, C20.1, C21.2, C22.2, C23.2, C24.2, C25.2, R10.2, U4.2 (GND), U5.9 (VSS), Y2.2 (GND), Y2.4 (GND); also elsewhere on the board
unnamed: C20.2, R9.1, Y2.3
unnamed: C18.1, D1.2 (A), R7.1, R8.2
unnamed: R10.1, U4.8 (RS)
unnamed: C21.1, R11.2, R12.1, U4.5 (VREF)
unnamed: C19.2, U5.8 (OSC1), Y2.1
unnamed: R9.2, U5.7 (OSC2)
unnamed: R7.2, U5.17 (~RESET)

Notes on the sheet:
Uses SPI0
Delay startup by ~5ns
bypass cap
Pullup
Use two vias for GND connection
Change slew rate, smaller R means faster rate of change, use it to reduce EMI
Split termination for reduced signal noise
Prevent ESD
Quick drain of C18
bulk cap
Can Transmitter
CAN Controller

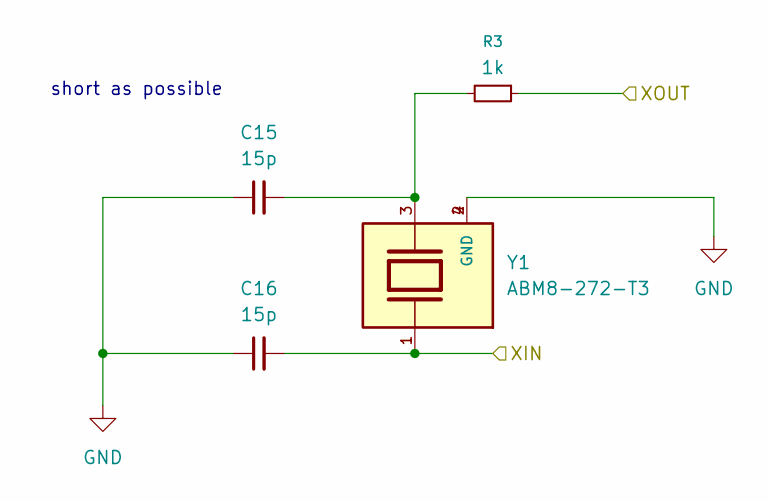
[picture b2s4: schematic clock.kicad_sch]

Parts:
C15, C16: 15p; C_0603_1608Metric_Pad1.08x0.95mm_HandSolder
R3: 1k; R_0603_1608Metric_Pad0.98x0.95mm_HandSolder
Y1: ABM8-272-T3; XTAL_ABM8-272-T3; PARTREV 07-29-20

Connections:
/clock/XIN: C16.2, Y1.1; also elsewhere on the board
/clock/XOUT: R3.1; also elsewhere on the board
GND: C15.1, C16.1, Y1.2 (GND), Y1.4 (GND); also elsewhere on the board
unnamed: C15.2, R3.2, Y1.3

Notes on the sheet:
short as possible
